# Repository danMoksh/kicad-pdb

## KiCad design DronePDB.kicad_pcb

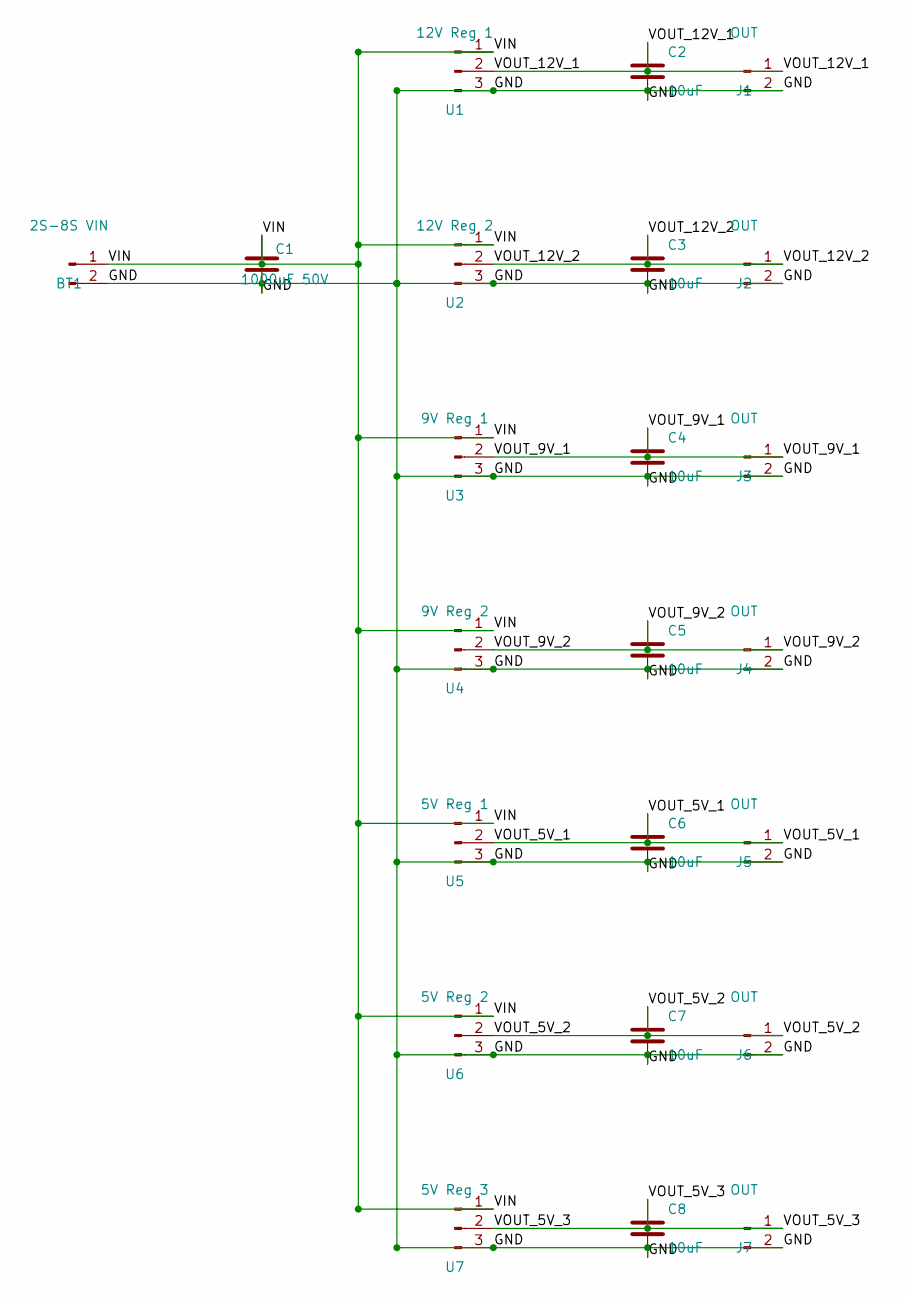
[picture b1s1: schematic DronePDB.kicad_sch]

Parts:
BT1: 2S-8S VIN; AMASS_XT60-M_1x02_P7.20mm_Vertical
C1: 1000uF 50V; CP_Radial_D8.0mm_P3.50mm
C2, C3, C4, C5, C6, C7, C8: 10uF; C_0805_2012Metric
J1, J2, J3, J4, J5, J6, J7: OUT; PinHeader_1x02_P2.54mm_Vertical
U1: 12V Reg 1; PinHeader_1x03_P2.54mm_Vertical
U2: 12V Reg 2; PinHeader_1x03_P2.54mm_Vertical
U3: 9V Reg 1; PinHeader_1x03_P2.54mm_Vertical
U4: 9V Reg 2; PinHeader_1x03_P2.54mm_Vertical
U5: 5V Reg 1; PinHeader_1x03_P2.54mm_Vertical
U6: 5V Reg 2; PinHeader_1x03_P2.54mm_Vertical
U7: 5V Reg 3; PinHeader_1x03_P2.54mm_Vertical

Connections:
GND: BT1.2, C1.2, C2.2, C3.2, C4.2, C5.2, C6.2, C7.2, C8.2, J1.2, J2.2, J3.2, J4.2, J5.2, J6.2, J7.2, U1.3, U2.3, U3.3, U4.3, U5.3, U6.3, U7.3
VIN: BT1.1, C1.1, U1.1, U2.1, U3.1, U4.1, U5.1, U6.1, U7.1
VOUT_5V_1: C6.1, J5.1, U5.2
VOUT_5V_2: C7.1, J6.1, U6.2
VOUT_5V_3: C8.1, J7.1, U7.2
VOUT_9V_1: C4.1, J3.1, U3.2
VOUT_9V_2: C5.1, J4.1, U4.2
VOUT_12V_1: C2.1, J1.1, U1.2
VOUT_12V_2: C3.1, J2.1, U2.2

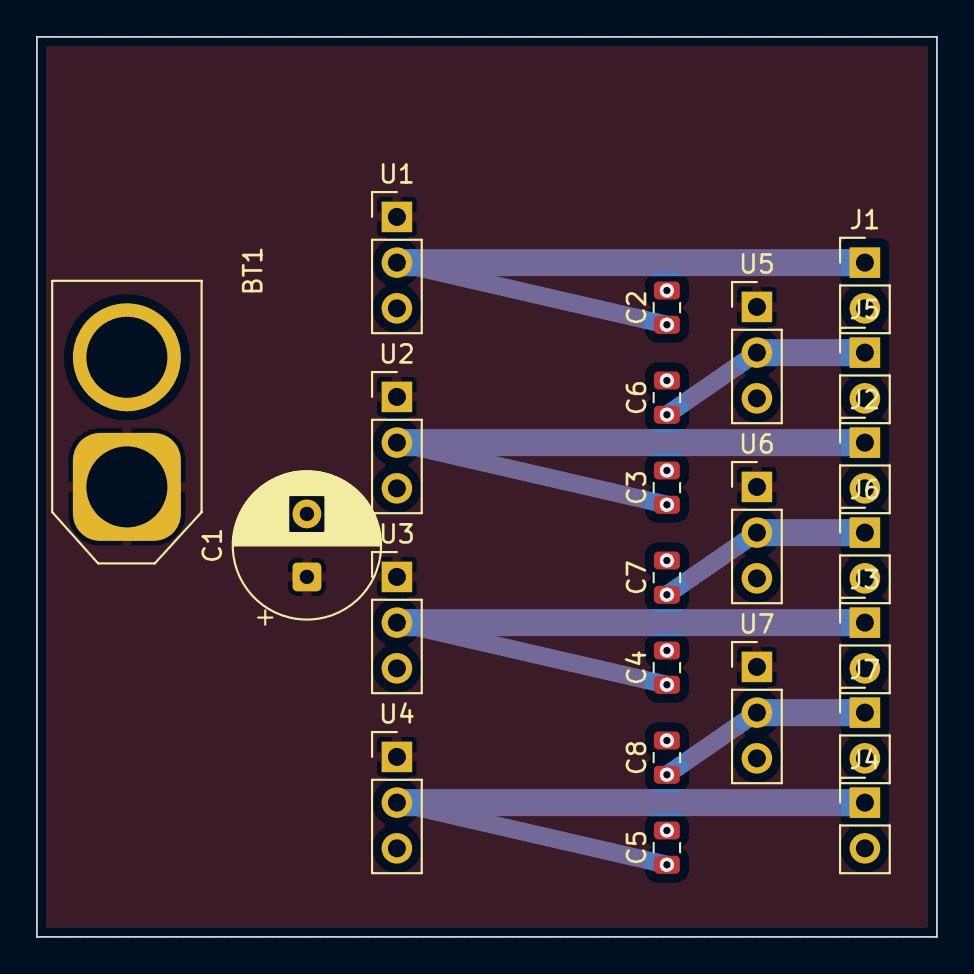
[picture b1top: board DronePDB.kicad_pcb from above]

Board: 2 copper layers, 50.0 x 50.0 mm, 23 parts (0 on the bottom side), 9 nets.

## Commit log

2026-06-10 feat: drone pdb schematic and routing
2026-06-10 drl and gbr pushed
